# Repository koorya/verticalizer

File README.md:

# Вертикализатор

Репозиторий включает в себя несколько направлений разработки.
 - Hardware - проект схемы и разводки модернизированной печатной платы панели прибора
 - Production - материалы, передаваемые в производство платы
 - Firmware - состоит из двух частей: plc_cp1l - проект прошики ПЛК, python - submodule с примером общений с прибором из ПК
 - CAD - чертежи корпусов устройства
 - Docs - справочная информация по используемым компонентам

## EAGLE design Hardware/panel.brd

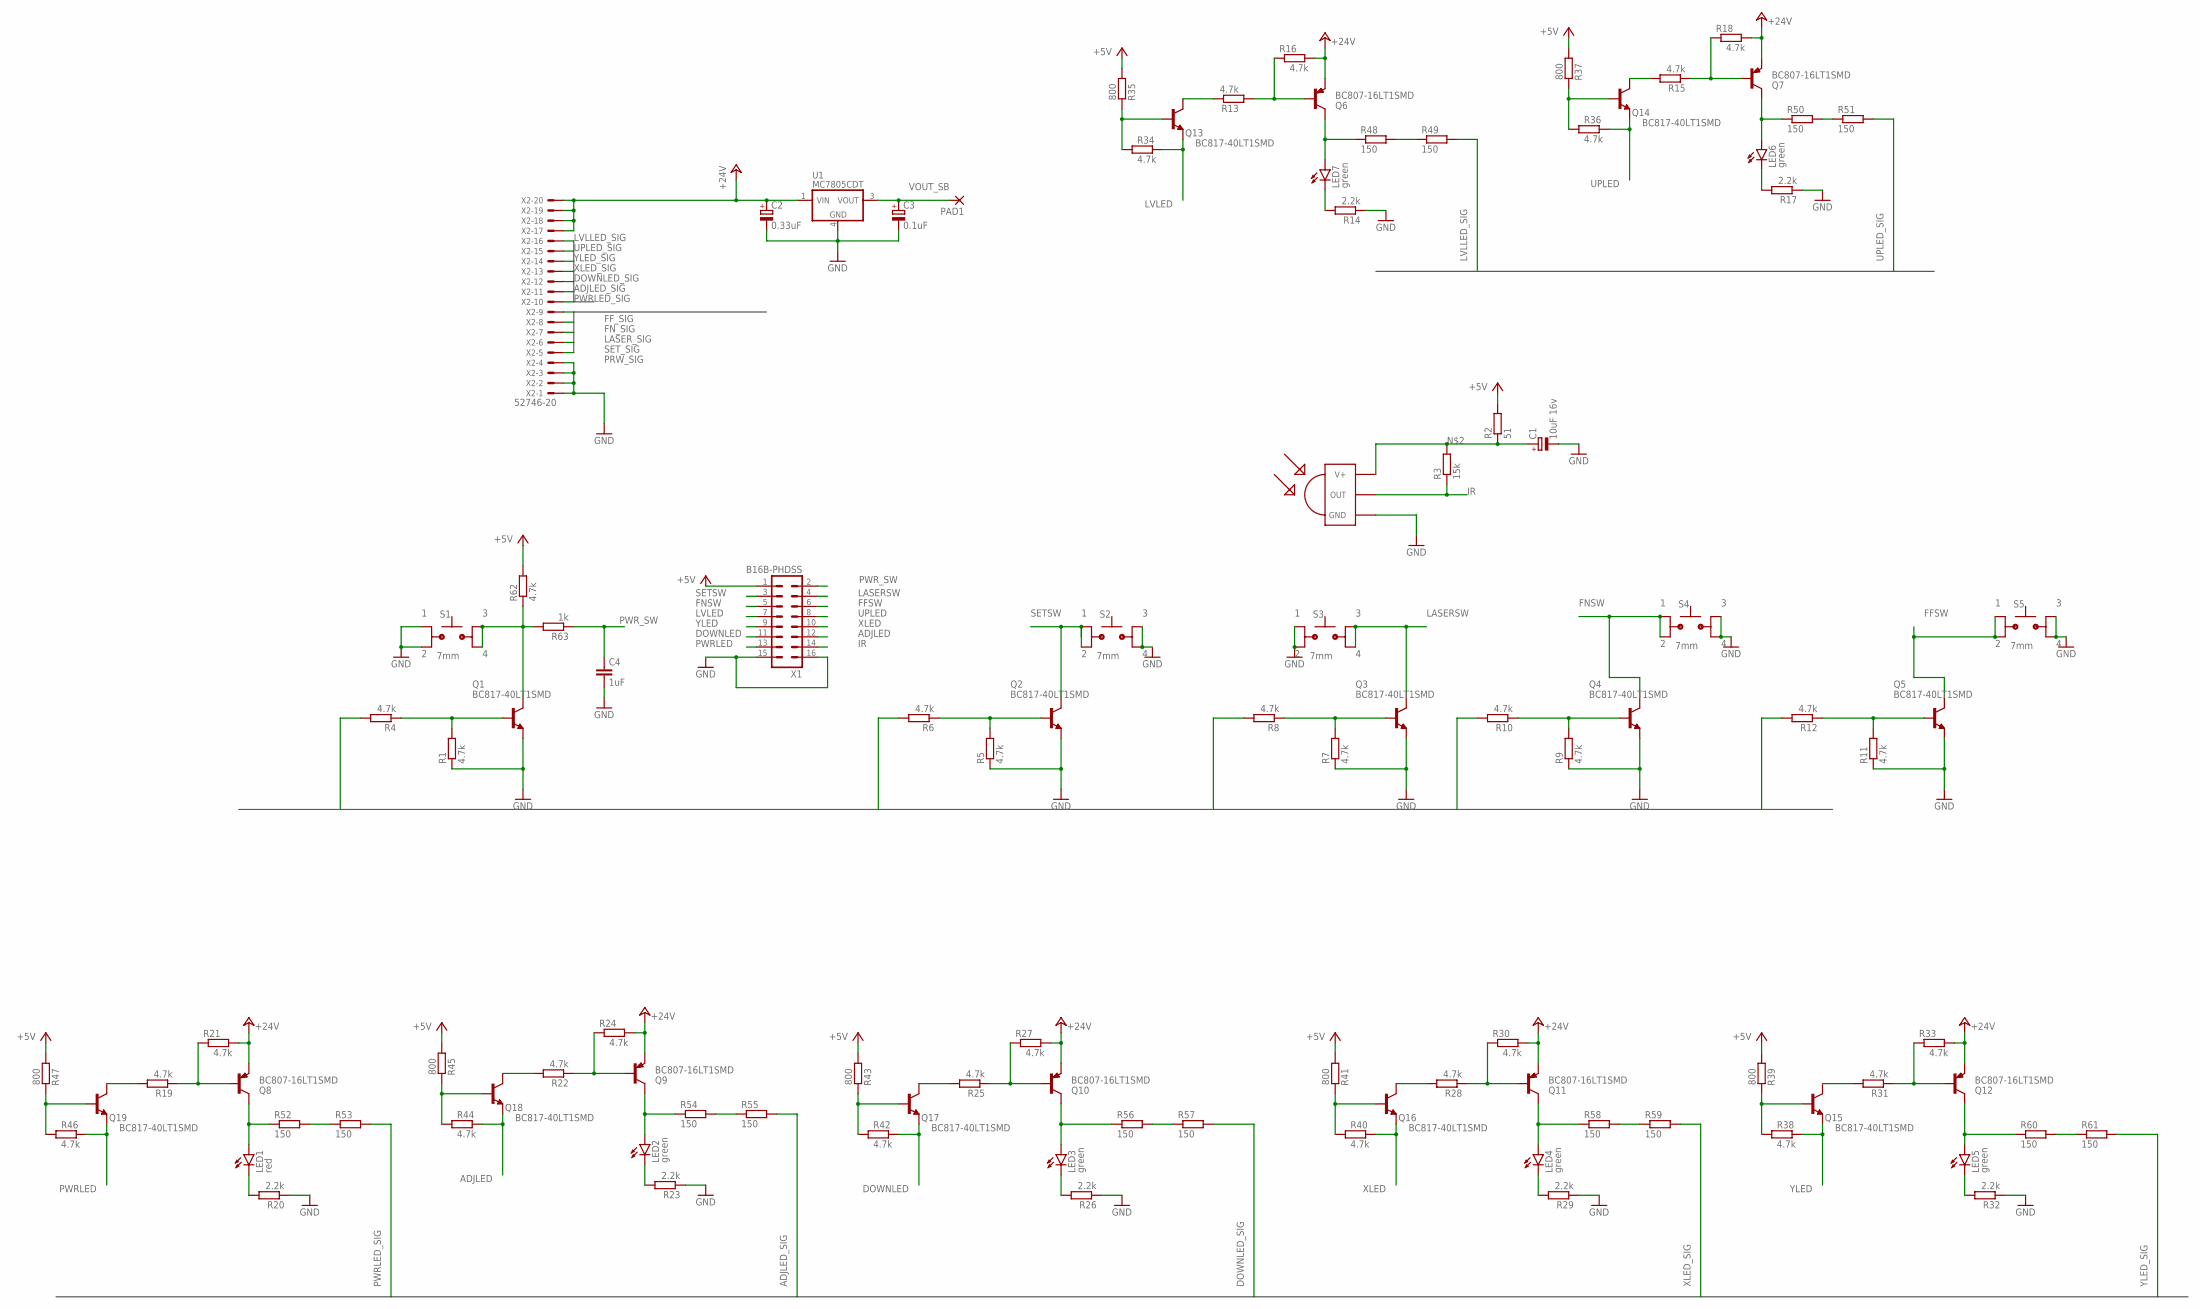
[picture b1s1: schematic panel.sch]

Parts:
C1: 10uF 16v; CT3216
C2: 0.33uF; CT3216
C3: 0.1uF; CT3216
C4: 1uF; C0805
LED1: red; LED_RED_3MM
LED2, LED3, LED4, LED5, LED6, LED7: green; LED_GREEN_3MM
PAD1: 1,6/0,8
Q1, Q2, Q3, Q4, Q5, Q13, Q14, Q15, Q16, Q17, Q18, Q19: BC817-40LT1SMD; SOT23-BEC
Q6, Q7, Q8, Q9, Q10, Q11, Q12: BC807-16LT1SMD; SOT23
R1, R4, R5, R6, R7, R8, R9, R10, R11, R12, R13, R15, R16, R18, R19, R21, R22, R24, R25, R27, R28, R30, R31, R33, R34, R36, R38, R40, R42, R44, R46, R62: 4.7k; R0805
R2: 51; R0805
R3: 15k; R0805
R14, R17, R20, R23, R26, R29, R32: 2.2k; R0805
R35, R37, R39, R41, R43, R45, R47: 800; R0805
R48, R49, R50, R51, R52, R53, R54, R55, R56, R57, R58, R59, R60, R61: 150; R2512
R63: 1k; R0805
S1, S2, S3, S4, S5: 7mm; TL1105F
U1: MC7805CDT; DPAK-3
U$1: TSOP4838FLAT; HDRVR14W64P250_1X14_2266X508X754B
X1: B16B-PHDSS
X2: 52746-20

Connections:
+5V: R2.2, R35.1, R37.1, R39.1, R41.1, R43.1, R45.1, R47.1, R62.2, X1.1
+24V: C2.+, Q6.2 (E), Q7.2 (E), Q8.2 (E), Q9.2 (E), Q10.2 (E), Q11.2 (E), Q12.2 (E), R16.2, R18.2, R21.2, R24.2, R27.2, R30.2, R33.2, U1.1 (VIN), X2.17, X2.18, X2.19, X2.20
ADJLED: Q18.E, R44.2, X1.12
ADJLED_SIG: R55.2, X2.11
DOWNLED: Q17.E, R42.2, X1.11
DOWNLED_SIG: R57.2, X2.12
FFSW: Q5.C, S5.1 (0), S5.3 (0), X1.6
FF_SIG: R12.2, X2.9
FNSW: Q4.C, S4.1 (0), S4.3 (0), X1.5
FN_SIG: R10.2, X2.8
GND: C1.-, C2.-, C3.-, C4.2, Q1.E, Q2.E, Q3.E, Q4.E, Q5.E, R1.1, R5.1, R7.1, R9.1, R11.1, R14.1, R17.1, R20.1, R23.1, R26.1, R29.1, R32.1, S1.1 (0), S1.3 (0), S2.2 (1), S2.4 (1), S3.1 (0), S3.3 (0), S4.2 (1), S4.4 (1), S5.2 (1), S5.4 (1), U1.4 (GND), U$1.GND, X1.15, X1.16, X2.1, X2.2, X2.3, X2.4
IR: R3.1, U$1.OUT, X1.14
LASERSW: Q3.C, S3.2 (1), S3.4 (1), X1.4
LASER_SIG: R8.2, X2.7
LVLED: Q13.E, R34.2, X1.7
LVLLED_SIG: R49.2, X2.16
unnamed: Q1.B, R1.2, R4.1
unnamed: C1.+, R2.1, R3.2, U$1.VCC (V+)
unnamed: LED7.A, Q6.3 (C), R48.1
unnamed: Q2.B, R5.2, R6.1
unnamed: Q3.B, R7.2, R8.1
unnamed: Q4.B, R9.2, R10.1
unnamed: Q5.B, R11.2, R12.1
unnamed: Q6.1 (B), R13.1, R16.1
unnamed: Q13.C, R13.2
unnamed: LED7.K (C), R14.2
unnamed: Q14.B, R36.1, R37.2
unnamed: Q7.1 (B), R15.1, R18.1
unnamed: LED6.K (C), R17.2
unnamed: Q8.1 (B), R19.1, R21.1
unnamed: LED1.K (C), R20.2
unnamed: Q9.1 (B), R22.1, R24.1
unnamed: LED2.K (C), R23.2
unnamed: Q10.1 (B), R25.1, R27.1
unnamed: LED3.K (C), R26.2
unnamed: Q11.1 (B), R28.1, R30.1
unnamed: LED4.K (C), R29.2
unnamed: Q12.1 (B), R31.1, R33.1
unnamed: LED5.K (C), R32.2
unnamed: Q13.B, R34.1, R35.2
unnamed: Q14.C, R15.2
unnamed: Q15.B, R38.1, R39.2
unnamed: Q15.C, R31.2
unnamed: Q16.B, R40.1, R41.2
unnamed: Q16.C, R28.2
unnamed: Q17.B, R42.1, R43.2
unnamed: Q17.C, R25.2
unnamed: Q18.B, R44.1, R45.2
unnamed: Q18.C, R22.2
unnamed: Q19.B, R46.1, R47.2
unnamed: Q19.C, R19.2
unnamed: R48.2, R49.1
unnamed: LED6.A, Q7.3 (C), R50.1
unnamed: R50.2, R51.1
unnamed: LED1.A, Q8.3 (C), R52.1
unnamed: R52.2, R53.1
unnamed: LED2.A, Q9.3 (C), R54.1
unnamed: R54.2, R55.1
unnamed: LED3.A, Q10.3 (C), R56.1
unnamed: R56.2, R57.1
unnamed: LED4.A, Q11.3 (C), R58.1
unnamed: R58.2, R59.1
unnamed: LED5.A, Q12.3 (C), R60.1
unnamed: R60.2, R61.1
unnamed: Q1.C, R62.1, R63.2, S1.2 (1), S1.4 (1)
PRW_SIG: R4.2, X2.5
PWRLED: Q19.E, R46.2, X1.13
PWRLED_SIG: R53.2, X2.10
PWR_SW: C4.1, R63.1, X1.2
SETSW: Q2.C, S2.1 (0), S2.3 (0), X1.3
SET_SIG: R6.2, X2.6
UPLED: Q14.E, R36.2, X1.8
UPLED_SIG: R51.2, X2.15
VOUT_SB: C3.+, PAD1.1, U1.3 (VOUT)
XLED: Q16.E, R40.2, X1.10
XLED_SIG: R59.2, X2.13
YLED: Q15.E, R38.2, X1.9
YLED_SIG: R61.2, X2.14

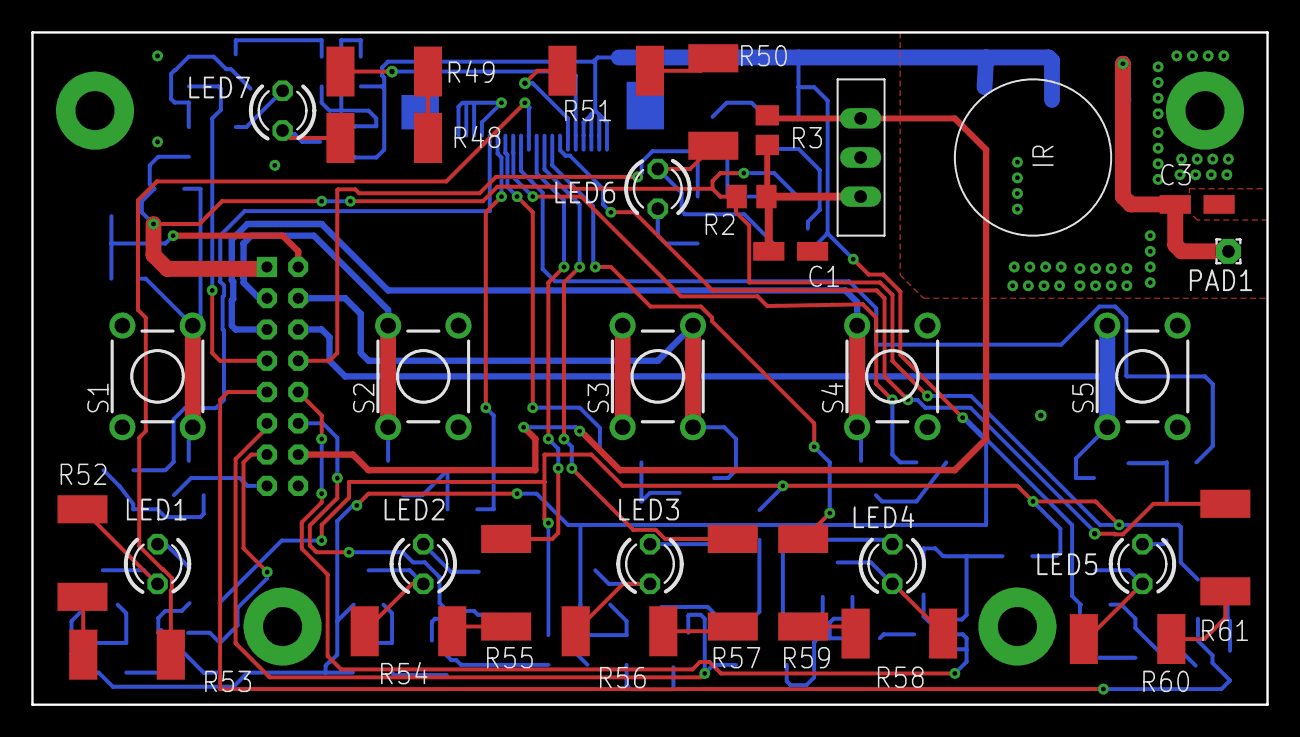
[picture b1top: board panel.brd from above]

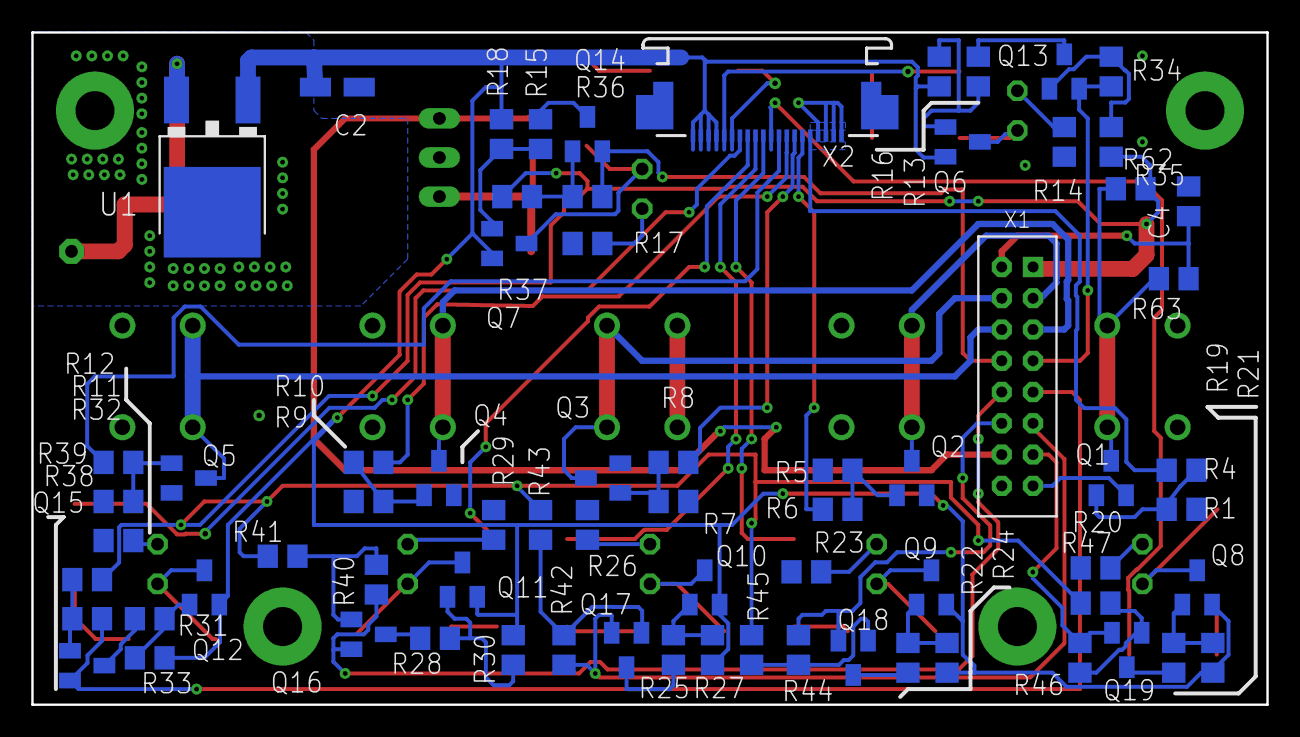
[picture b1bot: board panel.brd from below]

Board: 2 copper layers, 79.0 x 43.0 mm, 103 parts (71 on the bottom side), 78 nets.

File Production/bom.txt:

Partlist exported from C:/Users/Puakt/Documents/EAGLE/projects/verticalizer/Hardware/panel.sch at 18.06.2020 19:30

Qty Value          Device         Package                           Parts                                                                                                                                              Description                                                                                                   MF    MPN OC_FARNELL OC_NEWARK POPULARITY SPICEPREFIX
1                  1,6/0,8        1,6/0,8                           PAD1                                                                                                                                               THROUGH-HOLE PAD                                                                                                                             15                    
1   0.1uF          CPOL-EUCT3216  CT3216                            C3                                                                                                                                                 POLARIZED CAPACITOR, European symbol                                                                                                         1          C          
1   0.33uF         CPOL-EUCT3216  CT3216                            C2                                                                                                                                                 POLARIZED CAPACITOR, European symbol                                                                                                         1          C          
1   10uF 16v       CPOL-EUCT3216  CT3216                            C1                                                                                                                                                 POLARIZED CAPACITOR, European symbol                                                                                                         1          C          
14  150            R-EU_R2512     R2512                             R48, R49, R50, R51, R52, R53, R54, R55, R56, R57, R58, R59, R60, R61                                                                               RESISTOR, European symbol                                                                                                                    0          R          
1   15k            R-EU_R0805     R0805                             R3                                                                                                                                                 RESISTOR, European symbol                                                                                                                    86         R          
7   2.2k           R-EU_R0805     R0805                             R14, R17, R20, R23, R26, R29, R32                                                                                                                  RESISTOR, European symbol                                                                                                                    86         R          
31  4.7k           R-EU_R0805     R0805                             R1, R4, R5, R6, R7, R8, R9, R10, R11, R12, R13, R15, R16, R18, R19, R21, R22, R24, R25, R27, R28, R30, R31, R33, R34, R36, R38, R40, R42, R44, R46 RESISTOR, European symbol                                                                                                                    86         R          
1   51             R-EU_R0805     R0805                             R2                                                                                                                                                 RESISTOR, European symbol                                                                                                                    86         R          
1   52746-20       52746-20       52746-20                          X2                                                                                                                                                 FPC Connector ZIF for SMT 0.5mm                                                                               MOLEX     9786350    unknown   0                     
5   7mm            TL11057MM      TL1105F                           S1, S2, S3, S4, S5                                                                                                                                                                                                                                                                                                    
7   800            R-EU_R0805     R0805                             R35, R37, R39, R41, R43, R45, R47                                                                                                                  RESISTOR, European symbol                                                                                                                    86         R          
1   B16B-PHDSS     B16B-PHDSS     B16B-PHDSS                        X1                                                                                                                                                 JST PHD series header 2.00mm pitch disconnectable crimp style connectors, vertical (side entry type), 16 pins                                                      
7   BC807-16LT1SMD BC807-16LT1SMD SOT23                             Q6, Q7, Q8, Q9, Q10, Q11, Q12                                                                                                                      PNP Transistror                                                                                                                              0                     
12  BC817-40LT1SMD BC817-40LT1SMD SOT23-BEC                         Q1, Q2, Q3, Q4, Q5, Q13, Q14, Q15, Q16, Q17, Q18, Q19                                                                                              NPN Transistor                                                                                                                               10                    
1   MC7805CDT      MC7805CDT      DPAK-3                            U1                                                                                                                                                 78xx SMD (D2PAK, DPAK)                                                                                                                                             
1   TSOP4838FLAT   TSOP4838FLAT   HDRVR14W64P250_1X14_2266X508X754B U$1                                                                                                                                                IR Receiver and Demodulator                                                                                                                                        
6   green          LEDGREEN_3MM   LED_GREEN_3MM                     LED2, LED3, LED4, LED5, LED6, LED7                                                                                                                 LED                                                                                                                                                                
1   red            LEDRED_3MM     LED_RED_3MM                       LED1                                                                                                                                               LED

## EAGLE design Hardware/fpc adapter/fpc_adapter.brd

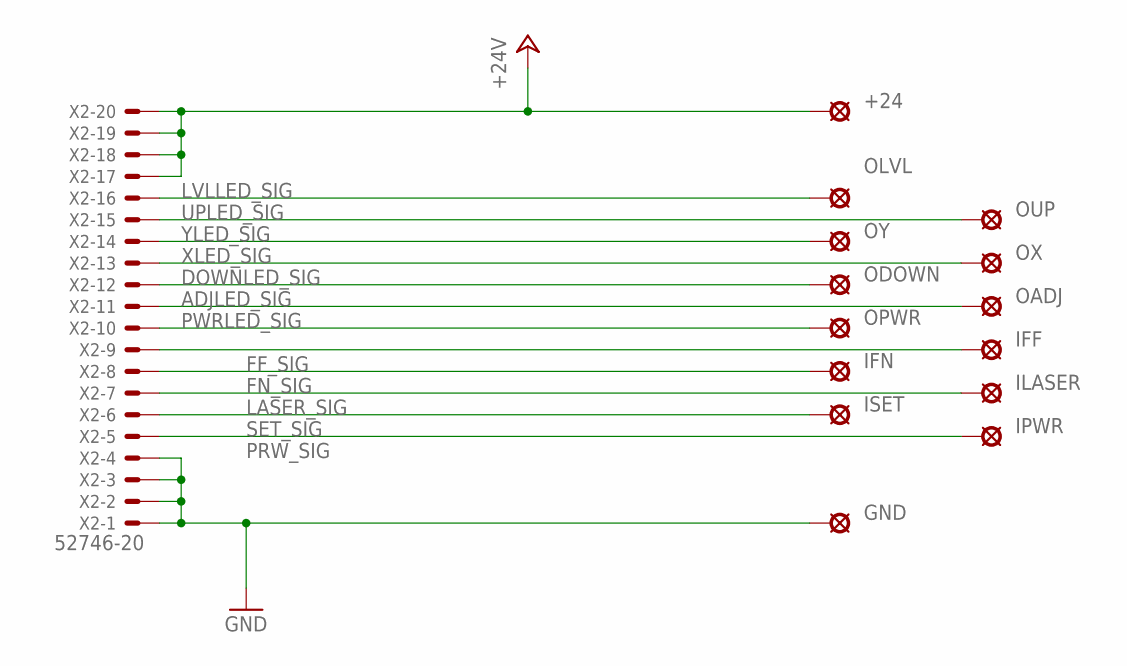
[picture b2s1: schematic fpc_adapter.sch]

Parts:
+24: LSP10
GND: LSP10
IFF: LSP10
IFN: LSP10
ILASER: LSP10
IPWR: LSP10
ISET: LSP10
OADJ: LSP10
ODOWN: LSP10
OLVL: LSP10
OPWR: LSP10
OUP: LSP10
OX: LSP10
OY: LSP10
X2: 52746-20

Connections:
+24V: +24.MP, X2.17, X2.18, X2.19, X2.20
ADJLED_SIG: OADJ.MP, X2.11
DOWNLED_SIG: ODOWN.MP, X2.12
FF_SIG: IFF.MP, X2.9
FN_SIG: IFN.MP, X2.8
GND: GND.MP, X2.1, X2.2, X2.3, X2.4
LASER_SIG: ILASER.MP, X2.7
LVLLED_SIG: OLVL.MP, X2.16
PRW_SIG: IPWR.MP, X2.5
PWRLED_SIG: OPWR.MP, X2.10
SET_SIG: ISET.MP, X2.6
UPLED_SIG: OUP.MP, X2.15
XLED_SIG: OX.MP, X2.13
YLED_SIG: OY.MP, X2.14

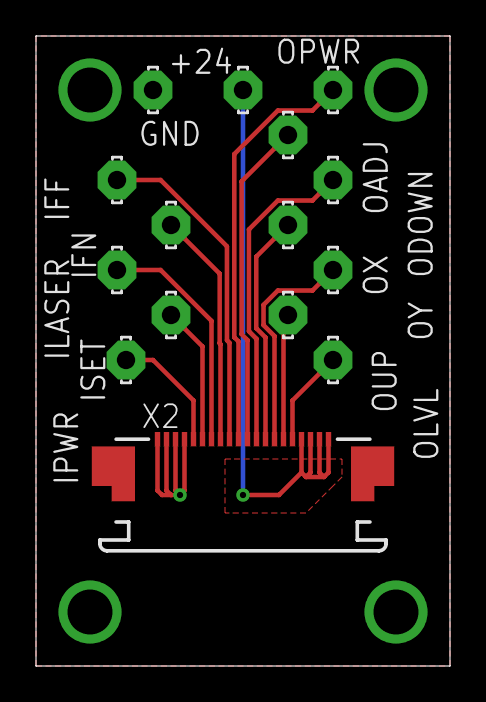
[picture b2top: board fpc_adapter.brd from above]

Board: 2 copper layers, 23.0 x 35.0 mm, 15 parts (0 on the bottom side), 14 nets.

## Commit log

2020-06-15 init commit
2020-06-15 test commit
2020-06-16 разъем под шлейф,вывод для штатного питания прибора. Сделал цепи комутации кнопок на транзисторе.
2020-06-16 переподключил индикаторы через транзисторы. это надо испытать
2020-06-16 сделал разводку управляющих и индикаторных цепей на транзисторах. еще не проверял работоспособность решений.
2020-06-16 заменил библиотеку transistor-pnp на пользовательскую, скопировав исходную. Таким образом ушел глюк с исчезновением корпусов транзисторов bc807
2020-06-16 нажал кнопку обновить библиотеки,чтобы компоненты на плате обновились
2020-06-17 изменил диаметры переходных отверстий с 0.35 на 0.3 мм
2020-06-17 убрал все, сделал тестовую схему эмуляции кнопки
2020-06-17 оставил только часть с индикатором и переразвел ее под макетную плату
2020-06-17 проверил работоспособность решения. нес защитный резистор от закоротки выхода на землю, чтоб не сгорал транзистор
2020-06-17 по результатам эксперимента с кнопками и индикаторами все нормально. оявилась идея добавить защитные резисторы на индикаторные выходы,чтобы не сгорал транзистор в случае кз на землю
2020-06-17 добавил файл печатной платы в stl чтобы проверить по отверстиям
2020-06-18 Создал схему и плату переходника с провода на шлейф
2020-06-18 сделал плату более узкой,чтоб она помещалась в дырку под разъем
2020-06-18 подготовил файлы для заказа в электроконнекте,а так же сделал пдф со списком компонентов
2020-06-22 по требованию с производства увеличил зазорполигона до 0,2мм на обеих платах. заказ переделал. заказе указал покрытие ПОС 63 вместо имерсионного олова
2020-06-22 заархивировал файлы заказа, именно этот архив сегодня я отправил по почте
2020-08-17 добавлен файл проект плк
2020-08-17 добавил RC-цепочку для устранения дребезга
2020-08-17 экспеиментально подобрал параметры цепочки кнопки питания, чтобы она срабатывала без проблем
2020-08-19 изменил программу плк,чтобы была возможность управлять им из скрипта на компьютере
2020-08-19 в качестве подмодуля добавил скрипт на питоне, позволяющий управлять прибором с компьютера
2020-09-30 добавлено две модели шестерен от новожилова
2020-09-30 указал, где искать файлы моделей
2020-09-30 удалил подмодуль
2020-09-30 добавил подмодуль
2021-03-22 добавил pdf со схемами и слоями
2021-03-23 добавил комментарии в программу для
2021-03-23 добавил gitignore в подмодуль
2021-03-23 добавил комментарии к программе на питоне
